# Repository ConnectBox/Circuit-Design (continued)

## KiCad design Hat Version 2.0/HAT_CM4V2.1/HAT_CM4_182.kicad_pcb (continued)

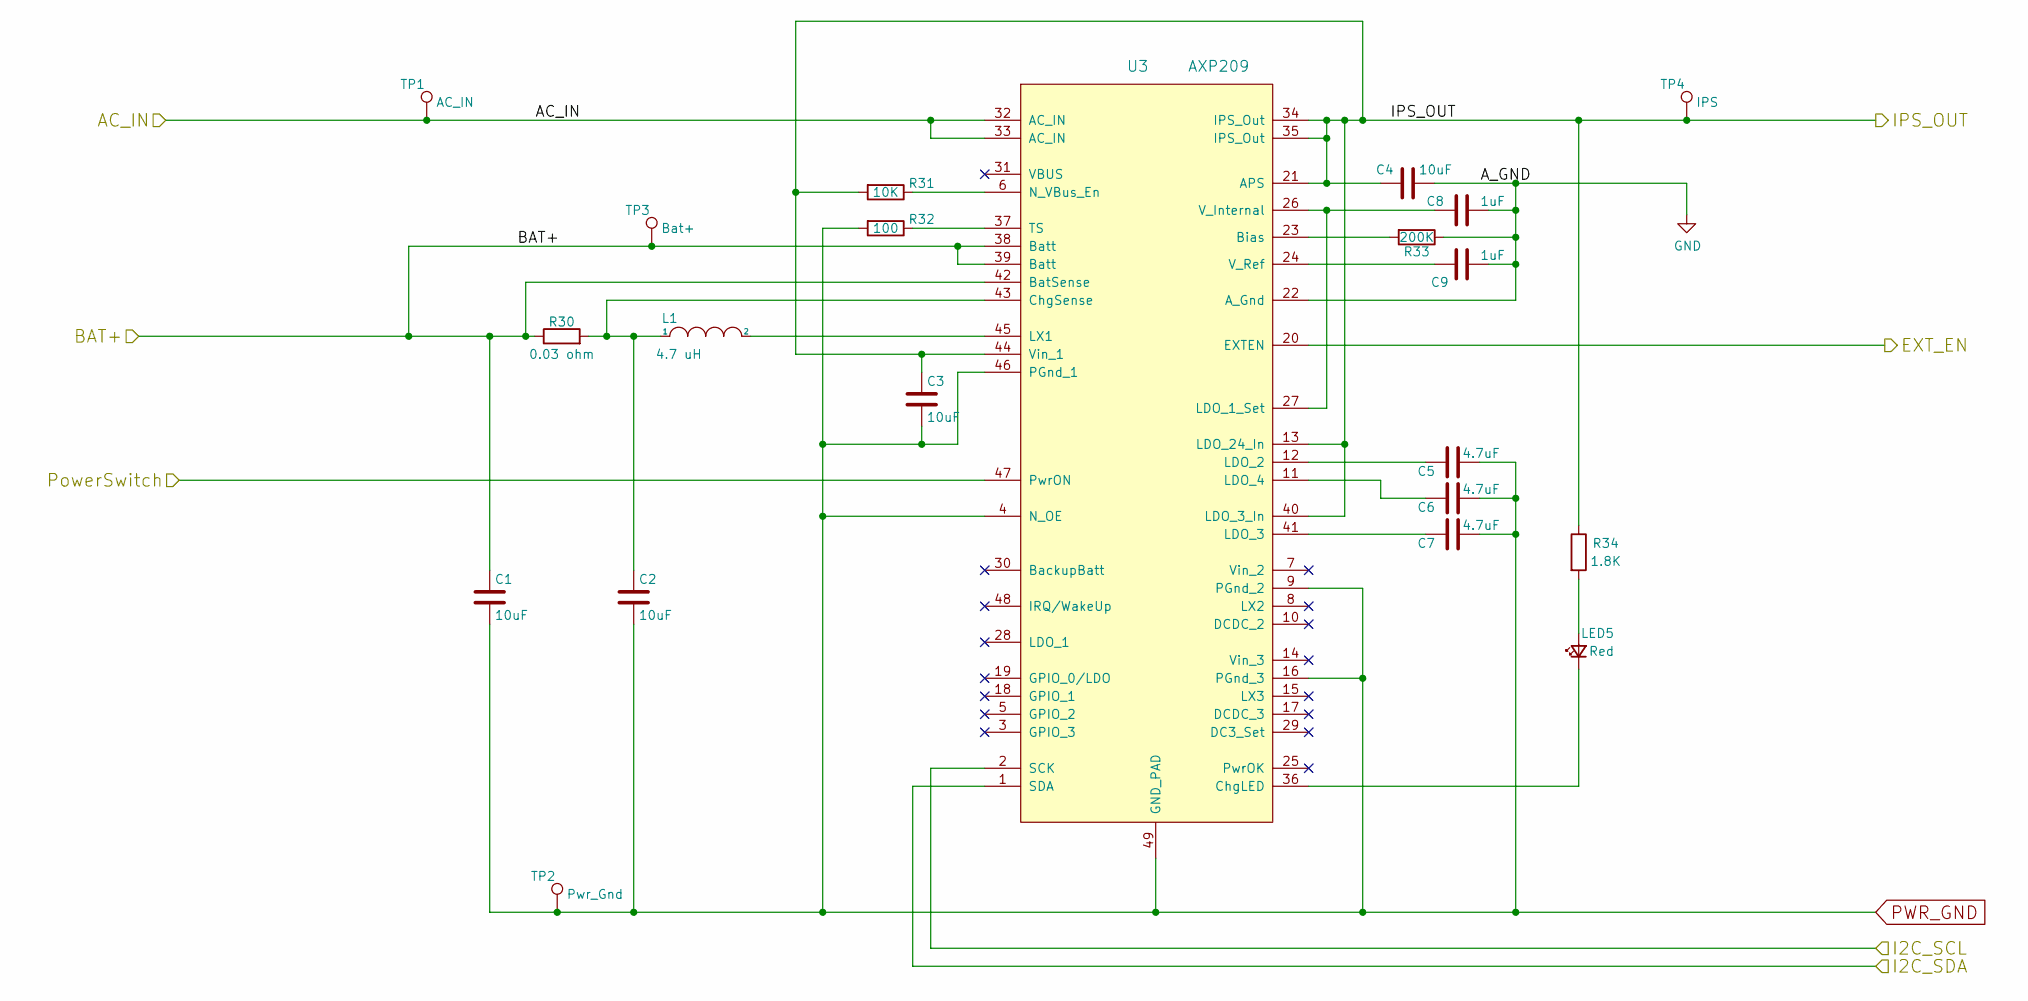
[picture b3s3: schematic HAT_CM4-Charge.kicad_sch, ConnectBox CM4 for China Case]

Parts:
C1, C2, C3, C4: 10uF; C_0603_1608Metric; Manufacturer P/N C0603C106M9PACTU; DigiKey P/N 399-C0603C106M9PAC7867CT-ND
C5, C6, C7: 4.7uF; C_0603_1608Metric; Manufacturer P/N C0603C475K9PACTU; DigiKey P/N 399-3482-1-ND
C8, C9: 1uF; C_0603_1608Metric; Manufacturer P/N CL10A105KQ8NNNC‎; DigiKey P/N 1276-1036-1-ND
L1: 4.7 uH; INDUCTOR_SMD_6x6-1; Manufacturer P/N NR6028T4R7M; DigiKey P/N 587-2100-1-ND
LED5: Red; LED_0603_1608Metric; Manufacturer P/N LTST-C191KRKT; DigiKey P/N 160-1447-1-ND
R30: 0.03 ohm; R_0603_1608Metric; Manufacturer P/N ERJ-3BWFR030V; DigiKey P/N P17466CT-ND
R31: 10K; R_0603_1608Metric; Manufacturer P/N RC0603FR-0710KL; DigiKey P/N 311-10.0KHRCT-ND
R32: 100; R_0603_1608Metric; Manufacturer P/N RC06-3FR-07100RL; DigiKey P/N 311-100HRCT-ND
R33: 200K; R_0603_1608Metric; Manufacturer P/N RC0603FR-07200KL; DigiKey P/N 311-200KHRCT-ND
R34: 1.8K; R_0603_1608Metric; Manufacturer P/N RC0603FR-071K8L; DigiKey P/N 311-1.80KHRCT-ND
TP1: AC_IN; TestPoint_THTPad_D1.5mm_Drill0.7mm
TP2: Pwr_Gnd; TestPoint_THTPad_D1.5mm_Drill0.7mm
TP3: Bat+; TestPoint_THTPad_D1.5mm_Drill0.7mm
TP4: IPS; TestPoint_THTPad_D1.5mm_Drill0.7mm
U3: AXP209; UQFN-48-1EP_6x6mm_Pitch0.4mm_75; Manufacturer P/N AXP209; DigiKey P/N [none - from AliExpress]

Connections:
/AC_IN: TP1.1, U3.32 (AC_IN), U3.33 (AC_IN); also elsewhere on the board
/Battery/BATT+: C1.1, R30.1, TP3.1, U3.38 (Batt), U3.39 (Batt), U3.42 (BatSense); also elsewhere on the board
/Battery/I2C_SCL: U3.2 (SCK); also elsewhere on the board
/Battery/I2C_SDA: U3.1 (SDA); also elsewhere on the board
/CM4_GPIO/EXT_ENA: U3.20 (EXTEN); also elsewhere on the board
/CM4_GPIO/PowerSwitch: U3.47 (PwrON); also elsewhere on the board
/Charger/IPS_OUT: C3.1, C4.1, R31.2, R34.1, TP4.1, U3.13 (LDO_24_In), U3.21 (APS), U3.34 (IPS_Out), U3.35 (IPS_Out), U3.40 (LDO_3_In), U3.44 (Vin_1); also elsewhere on the board
GND: C4.2, C8.1, C9.1, R33.1, U3.22 (A_Gnd); also elsewhere on the board
unnamed: C2.1, L1.1, R30.2, U3.43 (ChgSense)
unnamed: C5.2, U3.12 (LDO_2)
unnamed: C6.2, U3.11 (LDO_4)
unnamed: C7.2, U3.41 (LDO_3)
unnamed: C8.2, U3.26 (V_Internal), U3.27 (LDO_1_Set)
unnamed: C9.2, U3.24 (V_Ref)
unnamed: L1.2, U3.45 (LX1)
unnamed: LED5.1 (K), U3.36 (ChgLED)
unnamed: LED5.2 (A), R34.2
unnamed: R31.1, U3.6 (N_VBus_En)
unnamed: R32.1, U3.37 (TS)
unnamed: R33.2, U3.23 (Bias)
PWR_GND: C1.2, C2.2, C3.2, C5.1, C6.1, C7.1, R32.2, TP2.1, U3.4 (N_OE), U3.9 (PGnd_2), U3.16 (PGnd_3), U3.46 (PGnd_1), U3.49 (GND_PAD); also elsewhere on the board

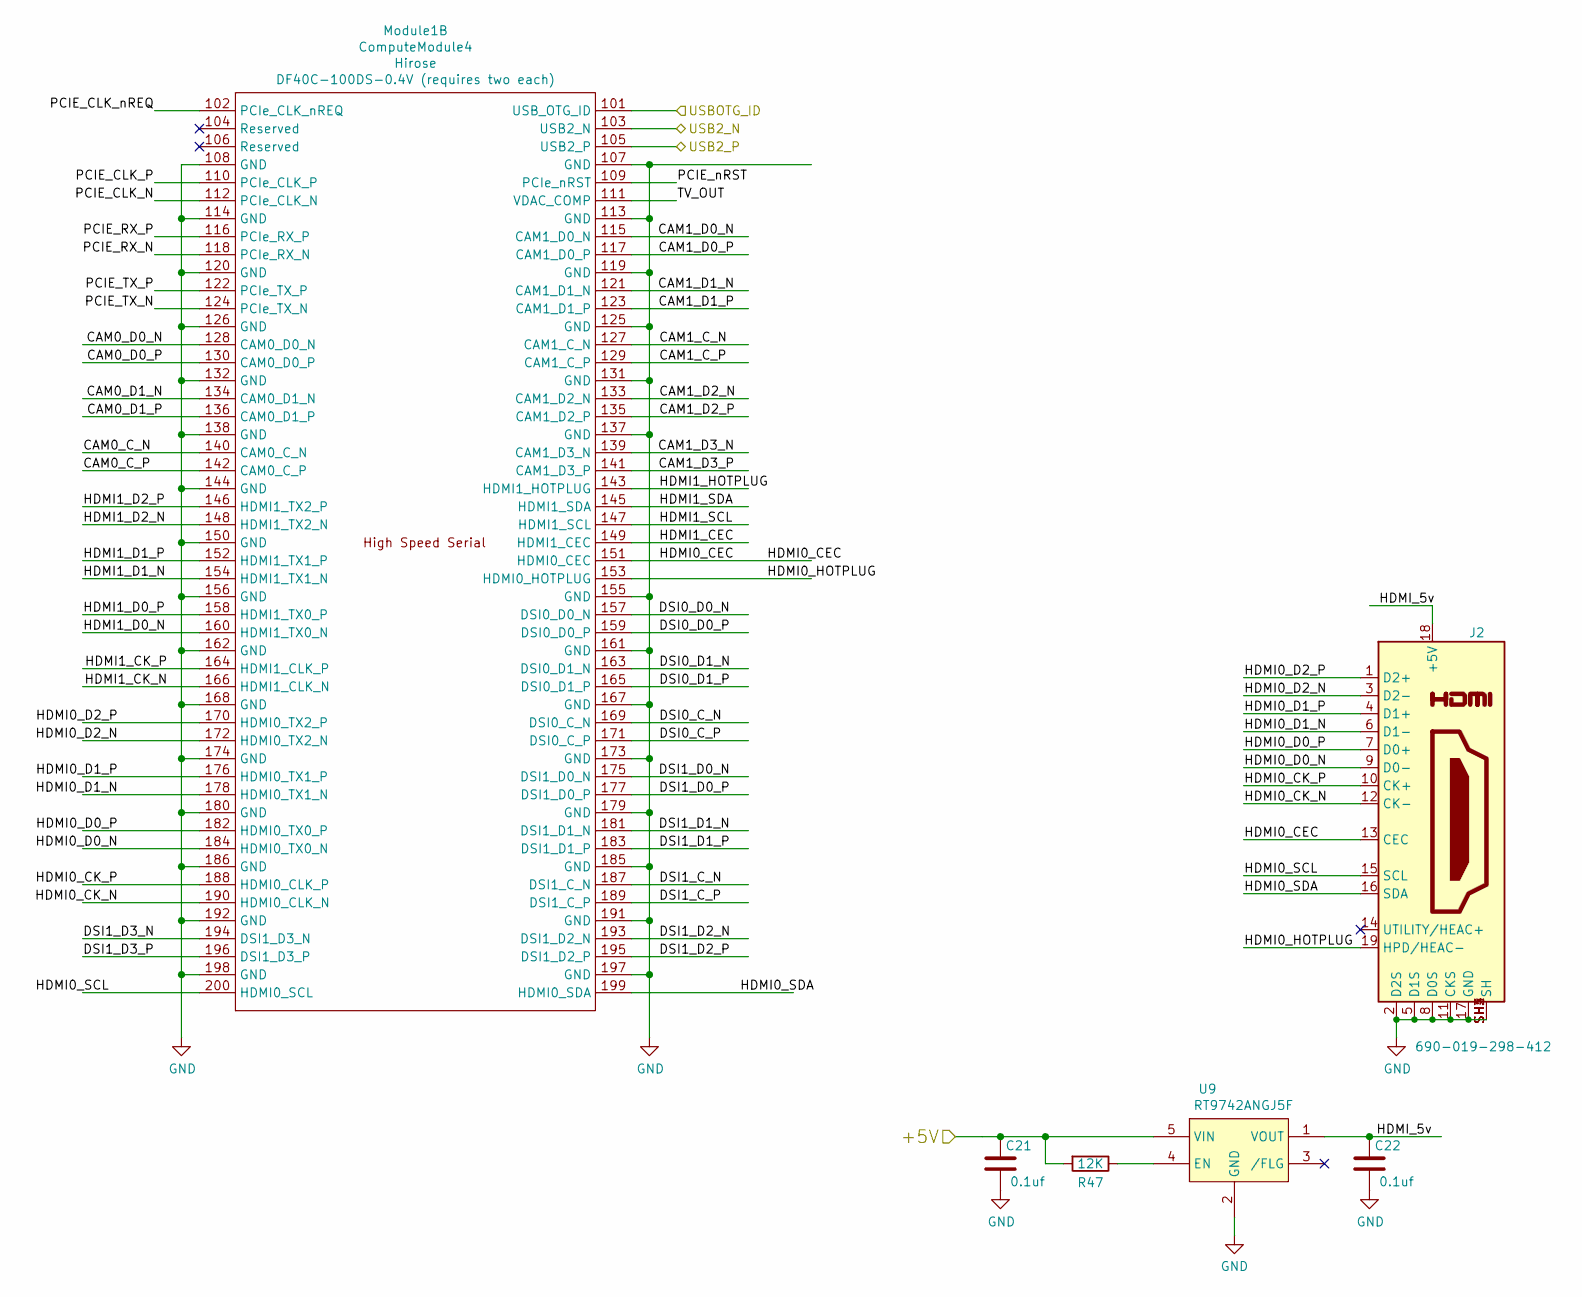
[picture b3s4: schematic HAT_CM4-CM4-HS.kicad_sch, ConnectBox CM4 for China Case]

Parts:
C21, C22: 0.1uf; C_0603_1608Metric; Manufacturer P/N C0603C104K9PAC7867; DigiKey P/N 399-17575-1-ND
J2: 690-019-298-412; HDMI_CnC_SMT; Manufacturer P/N 2000-1-2-41-00-BK; DigiKey P/N 1175-1703-ND
Module1: ComputeModule4; CM4_Module_noHoles; Manufacturer P/N DF40C-100DS-0.4V (requires two each); DigiKey P/N H11615CT-ND (requires two each)
R47: 12K; R_0603_1608Metric; Manufacturer P/N RC0603FR-12K2L; DigiKey P/N 311-12.0KHRCT-ND
U9: RT9742ANGJ5F; SOT-23-5; Manufacturer P/N RT9742ANGJ5F; DigiKey P/N 1028-1427-1-ND

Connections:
+5V: C21.1, R47.2, U9.5 (VIN); also elsewhere on the board
/CM4_HighSpeed/CAM0_C_N: Module1.140 (CAM0_C_N)
/CM4_HighSpeed/CAM0_C_P: Module1.142 (CAM0_C_P)
/CM4_HighSpeed/CAM0_D0_N: Module1.128 (CAM0_D0_N)
/CM4_HighSpeed/CAM0_D0_P: Module1.130 (CAM0_D0_P)
/CM4_HighSpeed/CAM0_D1_N: Module1.134 (CAM0_D1_N)
/CM4_HighSpeed/CAM0_D1_P: Module1.136 (CAM0_D1_P)
/CM4_HighSpeed/CAM1_C_N: Module1.127 (CAM1_C_N)
/CM4_HighSpeed/CAM1_C_P: Module1.129 (CAM1_C_P)
/CM4_HighSpeed/CAM1_D0_N: Module1.115 (CAM1_D0_N)
/CM4_HighSpeed/CAM1_D0_P: Module1.117 (CAM1_D0_P)
/CM4_HighSpeed/CAM1_D1_N: Module1.121 (CAM1_D1_N)
/CM4_HighSpeed/CAM1_D1_P: Module1.123 (CAM1_D1_P)
/CM4_HighSpeed/CAM1_D2_N: Module1.133 (CAM1_D2_N)
/CM4_HighSpeed/CAM1_D2_P: Module1.135 (CAM1_D2_P)
/CM4_HighSpeed/CAM1_D3_N: Module1.139 (CAM1_D3_N)
/CM4_HighSpeed/CAM1_D3_P: Module1.141 (CAM1_D3_P)
/CM4_HighSpeed/DSI0_C_N: Module1.169 (DSI0_C_N)
/CM4_HighSpeed/DSI0_C_P: Module1.171 (DSI0_C_P)
/CM4_HighSpeed/DSI0_D0_N: Module1.157 (DSI0_D0_N)
/CM4_HighSpeed/DSI0_D0_P: Module1.159 (DSI0_D0_P)
/CM4_HighSpeed/DSI0_D1_N: Module1.163 (DSI0_D1_N)
/CM4_HighSpeed/DSI0_D1_P: Module1.165 (DSI0_D1_P)
/CM4_HighSpeed/DSI1_C_N: Module1.187 (DSI1_C_N)
/CM4_HighSpeed/DSI1_C_P: Module1.189 (DSI1_C_P)
/CM4_HighSpeed/DSI1_D0_N: Module1.175 (DSI1_D0_N)
/CM4_HighSpeed/DSI1_D0_P: Module1.177 (DSI1_D0_P)
/CM4_HighSpeed/DSI1_D1_N: Module1.181 (DSI1_D1_N)
/CM4_HighSpeed/DSI1_D1_P: Module1.183 (DSI1_D1_P)
/CM4_HighSpeed/DSI1_D2_N: Module1.193 (DSI1_D2_N)
/CM4_HighSpeed/DSI1_D2_P: Module1.195 (DSI1_D2_P)
/CM4_HighSpeed/DSI1_D3_N: Module1.194 (DSI1_D3_N)
/CM4_HighSpeed/DSI1_D3_P: Module1.196 (DSI1_D3_P)
/CM4_HighSpeed/HDMI0_CEC: J2.13 (CEC), Module1.151 (HDMI0_CEC)
/CM4_HighSpeed/HDMI0_CK_N: J2.12 (CK-), Module1.190 (HDMI0_CLK_N)
/CM4_HighSpeed/HDMI0_CK_P: J2.10 (CK+), Module1.188 (HDMI0_CLK_P)
/CM4_HighSpeed/HDMI0_D0_N: J2.9 (D0-), Module1.184 (HDMI0_TX0_N)
/CM4_HighSpeed/HDMI0_D0_P: J2.7 (D0+), Module1.182 (HDMI0_TX0_P)
/CM4_HighSpeed/HDMI0_D1_N: J2.6 (D1-), Module1.178 (HDMI0_TX1_N)
/CM4_HighSpeed/HDMI0_D1_P: J2.4 (D1+), Module1.176 (HDMI0_TX1_P)
/CM4_HighSpeed/HDMI0_D2_N: J2.3 (D2-), Module1.172 (HDMI0_TX2_N)
/CM4_HighSpeed/HDMI0_D2_P: J2.1 (D2+), Module1.170 (HDMI0_TX2_P)
/CM4_HighSpeed/HDMI0_HOTPLUG: J2.19 (HPD/HEAC-), Module1.153 (HDMI0_HOTPLUG)
/CM4_HighSpeed/HDMI0_SCL: J2.15 (SCL), Module1.200 (HDMI0_SCL)
/CM4_HighSpeed/HDMI0_SDA: J2.16 (SDA), Module1.199 (HDMI0_SDA)
/CM4_HighSpeed/HDMI1_CEC: Module1.149 (HDMI1_CEC)
/CM4_HighSpeed/HDMI1_CK_N: Module1.166 (HDMI1_CLK_N)
/CM4_HighSpeed/HDMI1_CK_P: Module1.164 (HDMI1_CLK_P)
/CM4_HighSpeed/HDMI1_D0_N: Module1.160 (HDMI1_TX0_N)
/CM4_HighSpeed/HDMI1_D0_P: Module1.158 (HDMI1_TX0_P)
/CM4_HighSpeed/HDMI1_D1_N: Module1.154 (HDMI1_TX1_N)
/CM4_HighSpeed/HDMI1_D1_P: Module1.152 (HDMI1_TX1_P)
/CM4_HighSpeed/HDMI1_D2_N: Module1.148 (HDMI1_TX2_N)
/CM4_HighSpeed/HDMI1_D2_P: Module1.146 (HDMI1_TX2_P)
/CM4_HighSpeed/HDMI1_HOTPLUG: Module1.143 (HDMI1_HOTPLUG)
/CM4_HighSpeed/HDMI1_SCL: Module1.147 (HDMI1_SCL)
/CM4_HighSpeed/HDMI1_SDA: Module1.145 (HDMI1_SDA)
/CM4_HighSpeed/HDMI_5v: C22.1, J2.18 (+5V), U9.1 (VOUT)
/CM4_HighSpeed/PCIE_CLK_N: Module1.112 (PCIe_CLK_N)
/CM4_HighSpeed/PCIE_CLK_P: Module1.110 (PCIe_CLK_P)
/CM4_HighSpeed/PCIE_CLK_nREQ: Module1.102 (PCIe_CLK_nREQ)
/CM4_HighSpeed/PCIE_RX_N: Module1.118 (PCIe_RX_N)
/CM4_HighSpeed/PCIE_RX_P: Module1.116 (PCIe_RX_P)
/CM4_HighSpeed/PCIE_TX_N: Module1.124 (PCIe_TX_N)
/CM4_HighSpeed/PCIE_TX_P: Module1.122 (PCIe_TX_P)
/CM4_HighSpeed/PCIE_nRST: Module1.109 (PCIe_nRST)
/CM4_HighSpeed/TV_OUT: Module1.111 (VDAC_COMP)
/CM4_HighSpeed/USB2_N: Module1.103 (USB2_N); also elsewhere on the board
/CM4_HighSpeed/USB2_P: Module1.105 (USB2_P); also elsewhere on the board
/CM4_HighSpeed/USBOTG_ID: Module1.101 (USB_OTG_ID)
GND: C21.2, C22.2, J2.2 (D2S), J2.5 (D1S), J2.8 (D0S), J2.11 (CKS), J2.17 (GND), J2.SH1 (SH), J2.SH2 (SH), J2.SH3 (SH), J2.SH4 (SH), Module1.107 (GND), Module1.108 (GND), Module1.113 (GND), Module1.114 (GND), Module1.119 (GND), Module1.120 (GND), Module1.125 (GND), Module1.126 (GND), Module1.131 (GND), Module1.132 (GND), Module1.137 (GND), Module1.138 (GND), Module1.144 (GND), Module1.150 (GND), Module1.155 (GND), Module1.156 (GND), Module1.161 (GND), Module1.162 (GND), Module1.167 (GND), Module1.168 (GND), Module1.173 (GND), Module1.174 (GND), Module1.179 (GND), Module1.180 (GND), Module1.185 (GND), Module1.186 (GND), Module1.191 (GND), Module1.192 (GND), Module1.197 (GND), Module1.198 (GND), U9.2 (GND); also elsewhere on the board
unnamed: R47.1, U9.4 (EN)

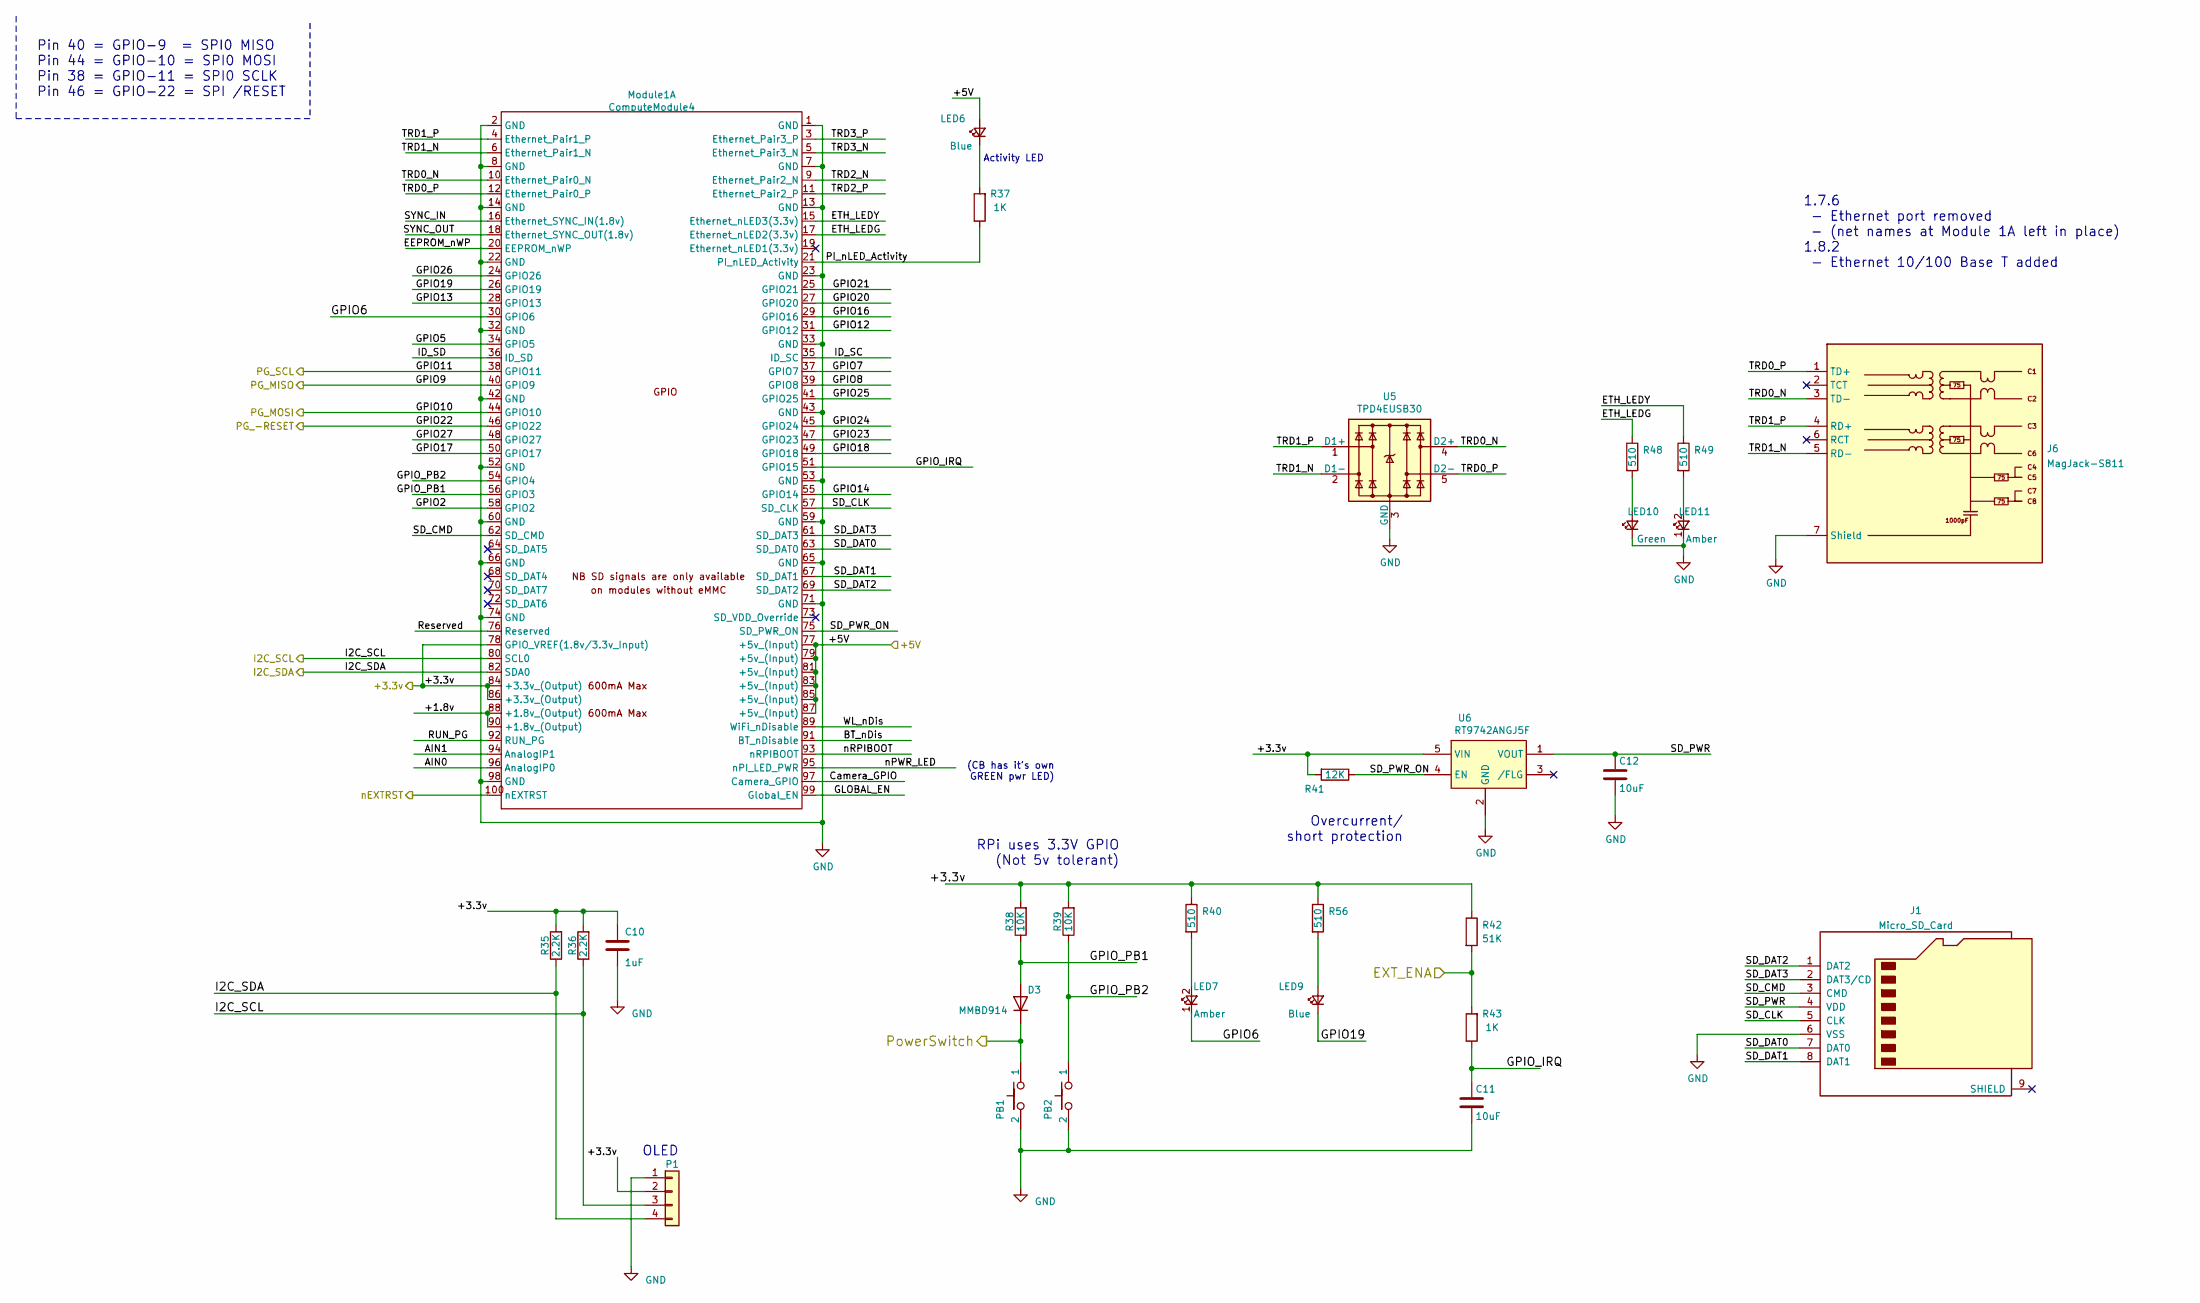
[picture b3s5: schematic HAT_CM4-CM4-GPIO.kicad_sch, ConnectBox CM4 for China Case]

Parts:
C10: 1uF; C_0603_1608Metric; Manufacturer P/N CL10A105KQ8NNNC‎; DigiKey P/N 1276-1036-1-ND
C11, C12: 10uF; C_0603_1608Metric; Manufacturer P/N C0603C106M9PACTU; DigiKey P/N 399-C0603C106M9PAC7867CT-ND
D3: MMBD914; D_SOT-23_ANK; Manufacturer P/N MMBD914LT1G; DigiKey P/N MMBD914LT1GOSCT-ND
J1: Micro_SD_Card; SDCARD_MOLEX_503398-1892; Manufacturer P/N 5033981892; DigiKey P/N WM11190CT-ND
J6: MagJack-S811; MagJack_S811; Manufacturer P/N S811-1X1T-06-F; DigiKey P/N 507-1456-1-ND
LED6, LED9: Blue; LED_0603_1608Metric; Manufacturer P/N IN-S63BT5B; DigiKey P/N 1830-1068-1-ND
LED7, LED11: Amber; LED_0603_1608Metric; Manufacturer P/N LTST-C191KFKT; DigiKey P/N 160-1445-1-ND
LED10: Green; LED_0603_1608Metric; Manufacturer P/N LTST-C191KFKT; DigiKey P/N 160-1446-1-ND
Module1: ComputeModule4; CM4_Module_noHoles; Manufacturer P/N DF40C-100DS-0.4V (requires two each); DigiKey P/N H11615CT-ND (requires two each)
P1: Conn_01x04; PinHeader_1x04_P2.54mm_Vertical
PB1, PB2: SPST-PUSH; SW-TL3330A; Manufacturer P/N TL3330AF130QG; DigiKey P/N EG4388CT-ND
R35, R36: 2.2K; R_0603_1608Metric; Manufacturer P/N RC0603FR-072K2L; DigiKey P/N 311-2.20KHRCT-ND
R37, R43: 1K; R_0603_1608Metric; Manufacturer P/N RC0603FR-071KL; DigiKey P/N 311-1.00KHRCT-ND
R38, R39: 10K; R_0603_1608Metric; Manufacturer P/N RC0603FR-0710KL; DigiKey P/N 311-10.0KHRCT-ND
R40, R48, R49, R56: 510; R_0603_1608Metric; Manufacturer P/N RC0603FR-07510RL; DigiKey P/N 311-510HRCT-ND
R41: 12K; R_0603_1608Metric; Manufacturer P/N RC0603FR-12K2L; DigiKey P/N 311-12.0KHRCT-ND
R42: 51K; R_0603_1608Metric; Manufacturer P/N RC0603FR-071KL; DigiKey P/N 311-51.0KHRCT-ND
U5: TPD4EUSB30; USON-10_2.5x1.0mm_P0.5mm; Manufacturer P/N TPD4EUSB30DQAR; DigiKey P/N 296-28063-1-ND
U6: RT9742ANGJ5F; SOT-23-5; Manufacturer P/N RT9742ANGJ5F; DigiKey P/N 1028-1427-1-ND

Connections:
+3.3v: C10.1, Module1.78 (GPIO_VREF(1.8v/3.3v_Input)), Module1.84 (+3.3v_(Output)), Module1.86 (+3.3v_(Output)), P1.2, R35.2, R36.2, R38.2, R39.2, R40.1, R41.2, R42.1, R56.1, U6.5 (VIN); also elsewhere on the board
+5V: LED6.2 (A), Module1.77 (+5v_(Input)), Module1.79 (+5v_(Input)), Module1.81 (+5v_(Input)), Module1.83 (+5v_(Input)), Module1.85 (+5v_(Input)), Module1.87 (+5v_(Input)); also elsewhere on the board
/Battery/I2C_SCL: Module1.80 (SCL0), P1.3, R36.1; also elsewhere on the board
/Battery/I2C_SDA: Module1.82 (SDA0), P1.4, R35.1; also elsewhere on the board
/Battery/MISO: Module1.40 (GPIO9); also elsewhere on the board
/Battery/MOSI: Module1.44 (GPIO10); also elsewhere on the board
/Battery/SCL: Module1.38 (GPIO11); also elsewhere on the board
/Battery//RESET: Module1.46 (GPIO22); also elsewhere on the board
/CM4_GPIO/+1.8v: Module1.88 (+1.8v_(Output)), Module1.90 (+1.8v_(Output))
/CM4_GPIO/AIN0: Module1.96 (AnalogIP0)
/CM4_GPIO/AIN1: Module1.94 (AnalogIP1)
/CM4_GPIO/BT_nDis: Module1.91 (BT_nDisable)
/CM4_GPIO/Camera_GPIO: Module1.97 (Camera_GPIO)
/CM4_GPIO/EEPROM_nWP: Module1.20 (EEPROM_nWP)
/CM4_GPIO/ETH_LEDG: Module1.17 (Ethernet_nLED2(3.3v)), R48.1
/CM4_GPIO/ETH_LEDY: Module1.15 (Ethernet_nLED3(3.3v)), R49.1
/CM4_GPIO/EXT_ENA: R42.2, R43.2; also elsewhere on the board
/CM4_GPIO/GLOBAL_EN: Module1.99 (Global_EN)
/CM4_GPIO/GPIO2: Module1.58 (GPIO2)
/CM4_GPIO/GPIO5: Module1.34 (GPIO5)
/CM4_GPIO/GPIO6: LED7.1 (K), Module1.30 (GPIO6)
/CM4_GPIO/GPIO7: Module1.37 (GPIO7)
/CM4_GPIO/GPIO8: Module1.39 (GPIO8)
/CM4_GPIO/GPIO12: Module1.31 (GPIO12)
/CM4_GPIO/GPIO13: Module1.28 (GPIO13)
/CM4_GPIO/GPIO14: Module1.55 (GPIO14)
/CM4_GPIO/GPIO16: Module1.29 (GPIO16)
/CM4_GPIO/GPIO17: Module1.50 (GPIO17)
/CM4_GPIO/GPIO18: Module1.49 (GPIO18)
/CM4_GPIO/GPIO19: LED9.1 (K), Module1.26 (GPIO19)
/CM4_GPIO/GPIO20: Module1.27 (GPIO20)
/CM4_GPIO/GPIO21: Module1.25 (GPIO21)
/CM4_GPIO/GPIO23: Module1.47 (GPIO23)
/CM4_GPIO/GPIO24: Module1.45 (GPIO24)
/CM4_GPIO/GPIO25: Module1.41 (GPIO25)
/CM4_GPIO/GPIO26: Module1.24 (GPIO26)
/CM4_GPIO/GPIO27: Module1.48 (GPIO27)
/CM4_GPIO/GPIO_IRQ: C11.1, Module1.51 (GPIO15), R43.1
/CM4_GPIO/GPIO_PB1: D3.2 (A), Module1.56 (GPIO3), R38.1
/CM4_GPIO/GPIO_PB2: Module1.54 (GPIO4), PB2.1, R39.1
/CM4_GPIO/ID_SC: Module1.35 (ID_SC)
/CM4_GPIO/ID_SD: Module1.36 (ID_SD)
/CM4_GPIO/PI_nLED_Activity: Module1.21 (PI_nLED_Activity), R37.1
/CM4_GPIO/PowerSwitch: D3.1 (K), PB1.1; also elsewhere on the board
/CM4_GPIO/RUN_PG: Module1.92 (RUN_PG)
/CM4_GPIO/Reserved: Module1.76 (Reserved)
/CM4_GPIO/SD_CLK: J1.5 (CLK), Module1.57 (SD_CLK)
/CM4_GPIO/SD_CMD: J1.3 (CMD), Module1.62 (SD_CMD)
/CM4_GPIO/SD_DAT0: J1.7 (DAT0), Module1.63 (SD_DAT0)
/CM4_GPIO/SD_DAT1: J1.8 (DAT1), Module1.67 (SD_DAT1)
/CM4_GPIO/SD_DAT2: J1.1 (DAT2), Module1.69 (SD_DAT2)
/CM4_GPIO/SD_DAT3: J1.2 (DAT3/CD), Module1.61 (SD_DAT3)
/CM4_GPIO/SD_PWR: C12.1, J1.4 (VDD), U6.1 (VOUT)
/CM4_GPIO/SD_PWR_ON: Module1.75 (SD_PWR_ON), R41.1, U6.4 (EN)
/CM4_GPIO/SYNC_IN: Module1.16 (Ethernet_SYNC_IN(1.8v))
/CM4_GPIO/SYNC_OUT: Module1.18 (Ethernet_SYNC_OUT(1.8v))
/CM4_GPIO/TRD0_N: J6.3 (TD-), Module1.10 (Ethernet_Pair0_N), U5.4 (D2+), U5.7
/CM4_GPIO/TRD0_P: J6.1 (TD+), Module1.12 (Ethernet_Pair0_P), U5.5 (D2-), U5.6
/CM4_GPIO/TRD1_N: J6.5 (RD-), Module1.6 (Ethernet_Pair1_N), U5.2 (D1-), U5.9
/CM4_GPIO/TRD1_P: J6.4 (RD+), Module1.4 (Ethernet_Pair1_P), U5.1 (D1+), U5.10
/CM4_GPIO/TRD2_N: Module1.9 (Ethernet_Pair2_N)
/CM4_GPIO/TRD2_P: Module1.11 (Ethernet_Pair2_P)
/CM4_GPIO/TRD3_N: Module1.5 (Ethernet_Pair3_N)
/CM4_GPIO/TRD3_P: Module1.3 (Ethernet_Pair3_P)
/CM4_GPIO/WL_nDis: Module1.89 (WiFi_nDisable)
/CM4_GPIO/nPWR_LED: Module1.95 (nPI_LED_PWR)
/CM4_GPIO/nRPIBOOT: Module1.93 (nRPIBOOT)
/USB Hub/nEXTRST: Module1.100 (nEXTRST); also elsewhere on the board
GND: C10.2, C11.2, C12.2, J1.6 (VSS), J6.7 (Shield), LED10.1 (K), LED11.1 (K), Module1.1 (GND), Module1.2 (GND), Module1.7 (GND), Module1.8 (GND), Module1.13 (GND), Module1.14 (GND), Module1.22 (GND), Module1.23 (GND), Module1.32 (GND), Module1.33 (GND), Module1.42 (GND), Module1.43 (GND), Module1.52 (GND), Module1.53 (GND), Module1.59 (GND), Module1.60 (GND), Module1.65 (GND), Module1.66 (GND), Module1.71 (GND), Module1.74 (GND), Module1.98 (GND), P1.1, PB1.2, PB2.2, U5.3 (GND), U5.8 (GND), U6.2 (GND); also elsewhere on the board
unnamed: LED7.2 (A), R40.2
unnamed: LED9.2 (A), R56.2
unnamed: LED10.2 (A), R48.2
unnamed: LED11.2 (A), R49.2
unnamed: LED6.1 (K), R37.2

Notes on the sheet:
1.7.6 - Ethernet port removed - (net names at Module 1A left in place) 1.8.2 - Ethernet 10/100 Base T added
Pin 40 = GPIO-9 = SPI0 MISO Pin 44 = GPIO-10 = SPI0 MOSI Pin 38 = GPIO-11 = SPI0 SCLK Pin 46 = GPIO-22 = SPI /RESET
RPi uses 3.3V GPIO (Not 5v tolerant)
Overcurrent/ short protection
OLED
Activity LED
(CB has it's own GREEN pwr LED)

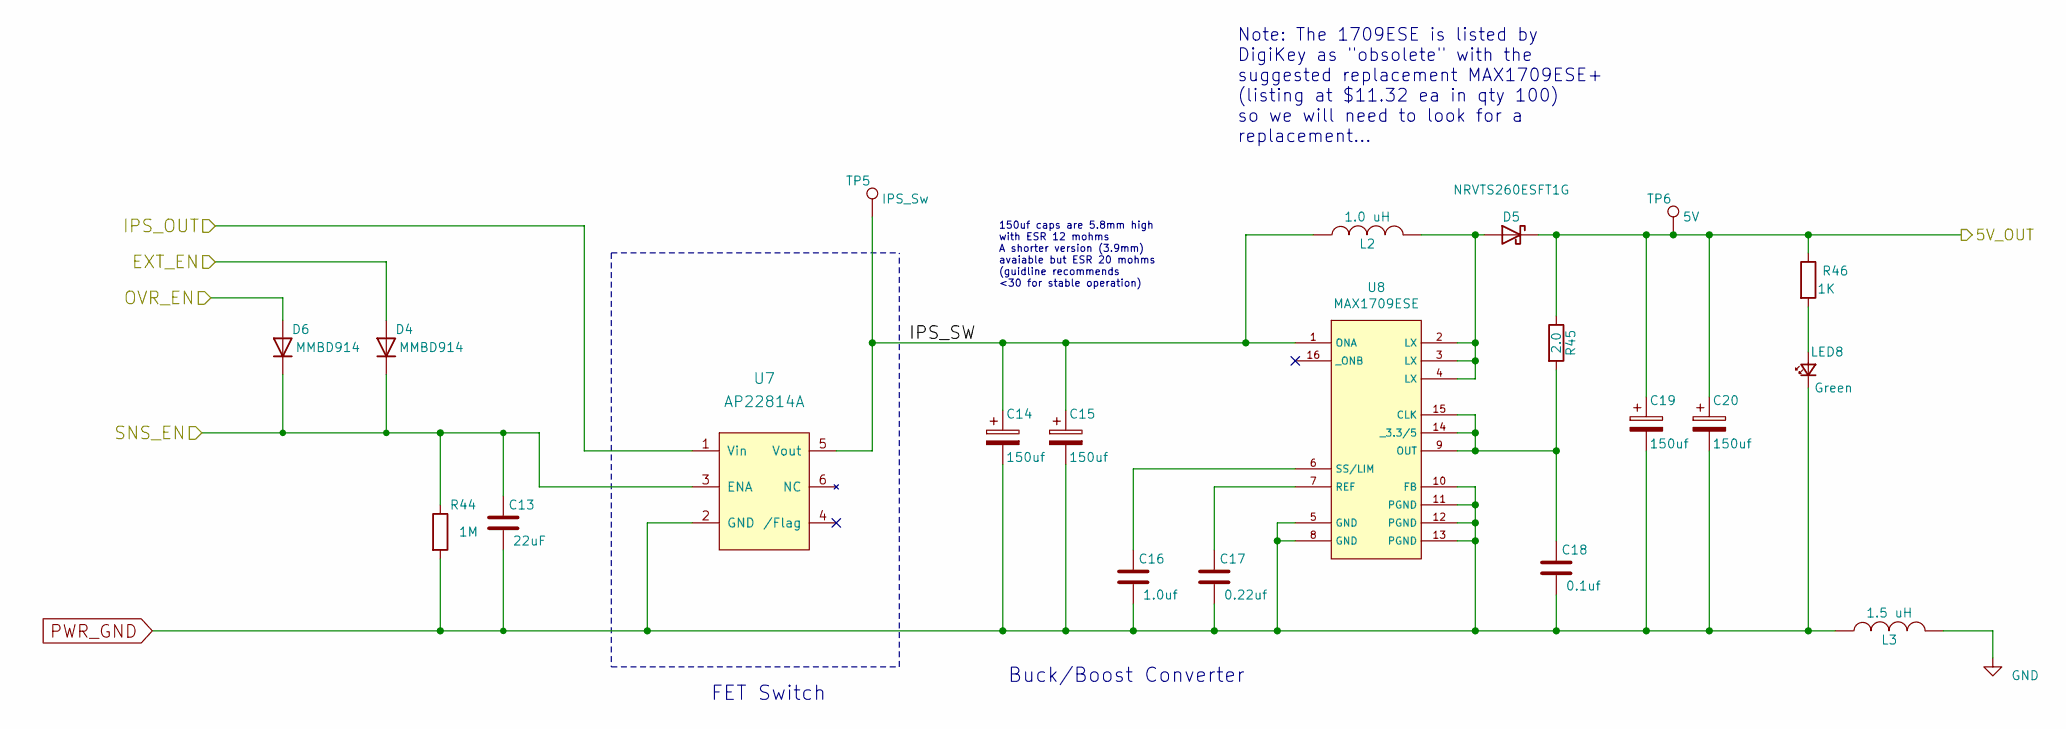
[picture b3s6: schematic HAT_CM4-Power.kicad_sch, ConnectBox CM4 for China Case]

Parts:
C13: 22uF; C_0603_1608Metric; Manufacturer P/N CL10A226MQ8NRNC; DigiKey P/N 1276-1193-1-ND
C14, C15, C19, C20: 150uf; CP_Elec_5x3; Manufacturer P/N APXF6R3ARA151ME61G; DigiKey P/N 565-4332-1-ND
C16: 1.0uf; C_0603_1608Metric; Manufacturer P/N C0603C105K9PACTU; DigiKey P/N 399-7848-1-ND
C17: 0.22uf; C_0603_1608Metric; Manufacturer P/N C0603C224K9PAC7867; DigiKey P/N 399-14969-1-ND
C18: 0.1uf; C_0603_1608Metric; Manufacturer P/N C0603C104K9PAC7867; DigiKey P/N 399-17575-1-ND
D4, D6: MMBD914; D_SOT-23_ANK; Manufacturer P/N MMBD914LT1G; DigiKey P/N MMBD914LT1GOSCT-ND
D5: NRVTS260ESFT1G; SOD-123FL; Manufacturer P/N NRVTS260ESFT1G; DigiKey P/N NRVTS260ESFT1GOSCT-ND
L2: 1.0 uH; L_Taiyo-Yuden_MD-5050; Manufacturer P/N LQH5BPN1R0N38L; DigiKey P/N 490-16290-1-ND - Cut Tape (CT)
L3: 1.5 uH; L_Taiyo-Yuden_NR-50xx; Manufacturer P/N NRS5020T1R5NMGJ; DigiKey P/N 587-2404-1-ND
LED8: Green; LED_0603_1608Metric; Manufacturer P/N LTST-C191KFKT; DigiKey P/N 160-1446-1-ND
R44: 1M; R_0603_1608Metric; Manufacturer P/N RC0603FR-071ML; DigiKey P/N 311-1.00MHRCT-ND
R45: 2.0; R_0603_1608Metric; Manufacturer P/N RC0603FR-072RL; DigiKey P/N 311-2.00HRCT-ND
R46: 1K; R_0603_1608Metric; Manufacturer P/N RC0603FR-071KL; DigiKey P/N 311-1.00KHRCT-ND
TP5: IPS_Sw; TestPoint_THTPad_D1.5mm_Drill0.7mm
TP6: 5V; TestPoint_THTPad_D1.5mm_Drill0.7mm
U7: AP22814A; U-DFN2020-6; Manufacturer P/N AP22814ASN-7; DigiKey P/N AP22814ASN-7DICT-ND
U8: MAX1709ESE; SOP-16_3.9x9.9mm_P1.27mm; Manufacturer P/N MAX1709ESE; DigiKey P/N [none - from AliExpress]

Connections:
+5V: C19.1, C20.1, D5.1 (K), R45.1, R46.1, TP6.1; also elsewhere on the board
/CM4_GPIO/EXT_ENA: D4.2 (A); also elsewhere on the board
/Charger/IPS_OUT: U7.1 (Vin); also elsewhere on the board
/Power/IPS_SW: C14.1, C15.1, L2.1, TP5.1, U7.5 (Vout), U8.1 (ONA)
/Power/OVR_EN: D6.2 (A)
/Power/SNS_EN: C13.1, D4.1 (K), D6.1 (K), R44.1, U7.3 (ENA)
GND: L3.2; also elsewhere on the board
unnamed: C16.1, U8.6 (SS/LIM)
unnamed: C17.1, U8.7 (REF)
unnamed: C18.1, R45.2, U8.9 (OUT), U8.14 (_3.3/5), U8.15 (CLK)
unnamed: D5.2 (A), L2.2, U8.2 (LX), U8.3 (LX), U8.4 (LX)
unnamed: LED8.2 (A), R46.2
PWR_GND: C13.2, C14.2, C15.2, C16.2, C17.2, C18.2, C19.2, C20.2, L3.1, LED8.1 (K), R44.2, U7.2 (GND), U8.5 (GND), U8.8 (GND), U8.10 (FB), U8.11 (PGND), U8.12 (PGND), U8.13 (PGND); also elsewhere on the board

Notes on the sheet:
150uf caps are 5.8mm high with ESR 12 mohms A shorter version (3.9mm) avaiable but ESR 20 mohms (guidline recommends <30 for stable operation)
Buck/Boost Converter
Note: The 1709ESE is listed by DigiKey as "obsolete" with the suggested replacement MAX1709ESE+ (listing at $11.32 ea in qty 100) so we will need to look for a replacement...
FET Switch
